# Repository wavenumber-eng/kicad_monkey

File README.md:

# KiCad Monkey

```text
            ▓▓▓▓▓▓▓▓▓▓
          ▓▓▓▓▓▓▓▓▓▓▓▓▓▓
        ▓▓▓▓▓▓▓▓▓▓▓▓▓▓▓▓▓▓
      ▓▓▓▓░░░░░░▓▓░░░░░░▓▓▓▓
  ░░░░▓▓░░░░░░░░░░░░░░░░░░▓▓░░░░
  ░░░░▓▓░░    ░░░░░░    ░░▓▓░░░░
    ░░▓▓░░  ██░░░░░░  ██░░▓▓░░
      ▓▓░░░░░░░░░░░░░░░░░░▓▓
        ▓▓░░░░░░░░░░░░░░▓▓
          ▓▓▓▓░░░░░░▓▓▓▓
  ░░          ▓▓▓▓▓▓
    ▓▓      ▓▓▓▓▓▓▓▓▓▓
    ▓▓▓▓    ▓▓▓▓▓▓▓▓▓▓
      ▓▓▓▓▓▓▓▓▓▓▓▓▓▓▓▓▓▓
          ▓▓▓▓░░▓▓░░▓▓▓▓
```

`kicad_monkey` is a focused Python package for KiCad source-file parsing,
round-trip modeling, close-to-format utilities, and IR-backed 2D rendering.

Use it when you need Python code to inspect or modify KiCad files directly:

- read `.kicad_pro`, `.kicad_sch`, `.kicad_pcb`, `.kicad_sym`, and
  `.kicad_mod` files;
- query schematic and PCB objects through typed model facades;
- compile KiCad-native design netlists and design JSON;
- render schematic, PCB, symbol, and footprint views through plotter IR and SVG;
- make focused model edits, then write KiCad files back out.

This package is the low-level parser/model/rendering library. The same
repository also contains the separately published `kicad-cruncher` workflow
CLI under `packages/kicad_cruncher/`. The CLI depends on Monkey; Monkey never
depends on the CLI.

The Rust port has closed its Plotter-IR boundary and its bounded Windows x64
native Cruncher delivery milestone. See
the [native Cruncher delivery audit](docs/design/rust-phase6-native-cruncher-audit.html).
The accepted [native base SVG slice](docs/design/rust-native-svg-phase6-slice.html)
is followed by the accepted
[Windows no-fallback PCB physical provider](docs/design/rust-native-physical-provider-phase6-slice.html),
which retains Cruncher-owned enrichment and composition while replacing its
physical-base serialization seam. The accepted
[source-bound native design-facts slice](docs/design/rust-native-design-facts-phase6-slice.html)
next switches the Windows compiled graph and version-E netlist while retaining
Python Design JSON, netlist JSON, presentation, and orchestration. The
[accepted native-backed CLI compatibility slice](docs/design/rust-native-full-cli-phase6-slice.html)
governs the installed entry points, primary design aliases, artifact tree,
logs, exits, and no-fallback failures without claiming a separate all-Rust
Cruncher executable. The accepted
[Windows x64 release exit](docs/design/rust-phase6-exit.html) binds one tested
candidate set to CI and release publication. That milestone remains the
historical native-provider boundary: Linux and macOS retained the established
Python provider path, and Python still owned Cruncher orchestration and
presentation.

The accepted
[pure-Rust design CLI follow-on](packages/kicad_cruncher/docs/design/rust-cli-phase7-audit.html)
now supersedes that boundary for the Windows x64 `design`, `design-review`, and
`dr` vertical slice. Release archives contain Python-free `kicad-cruncher` and
`kcr` executables that own the complete review-bundle orchestration and
transactional publication path, plus version reporting. This is deliberately
not an all-command or all-platform Rust claim: other Cruncher commands remain
available through the universal Python wheel and `python -m kicad_cruncher`,
and Monkey remains the reusable lower-level library rather than depending on
Cruncher.

## Install

For library use inside an existing Python environment:

```powershell
pip install kicad-monkey
```

For development:

```powershell
git clone https://github.com/wavenumber-eng/kicad_monkey.git
cd kicad_monkey
uv sync --extra test
```

To develop and validate both public distributions from one checkout:

```powershell
uv sync --all-packages --all-extras
uv run --package kicad-cruncher kicad-cruncher --help
uv run --all-packages --all-extras python -m pytest tests/cross_package -q
```

## Quick Examples

### Load A Design And Inspect Nets

```python
from kicad_monkey import KiCadDesign

design = KiCadDesign.from_project_file("hardware/demo.kicad_pro")
netlist = design.to_netlist()

for net in netlist.nets:
    terminals = ", ".join(
        f"{terminal.designator}.{terminal.pin}"
        for terminal in net.terminals
    )
    print(f"{net.name}: {terminals}")
```

Save the KiCad-native design JSON used by higher-level review tools:

```python
from pathlib import Path

Path("build").mkdir(parents=True, exist_ok=True)
design.save_json("build/design.json")
```

### Render PCB SVG

```python
from pathlib import Path

from kicad_monkey import KiCadDesign

design = KiCadDesign.from_project_file("hardware/demo.kicad_pro")

out_dir = Path("build/svg")
out_dir.mkdir(parents=True, exist_ok=True)

svg = design.to_pcb_svg(
    layers=["Edge.Cuts", "F.Cu", "F.SilkS"],
    profile="enriched",
)
(out_dir / "front-copper.svg").write_text(svg, encoding="utf-8")
```

Use `profile="oracle"` when comparing against KiCad CLI output. Use
`profile="enriched"` when an app needs metadata on SVG elements. PCB SVG
rendering builds the board render IR before applying `layers=`, so layer
filters reduce output size but do not avoid full PCB parse or IR-build cost.

### Render Every Schematic Sheet Instance

Hierarchical designs can instantiate one `.kicad_sch` file more than once.
`KiCadSchematicInstance` represents each concrete sheet view.

```python
from pathlib import Path

from kicad_monkey import KiCadDesign, render_ir_to_svg

design = KiCadDesign.from_project_file("hardware/demo.kicad_pro")

out_dir = Path("build/schematic-svg")
out_dir.mkdir(parents=True, exist_ok=True)

for sheet in design.schematic_instances():
    doc = design.to_schematic_instance_ir(sheet)
    svg = render_ir_to_svg(doc)
    safe_name = sheet.sheet_name.replace("/", "_").replace("\\", "_")
    (out_dir / f"{sheet.instance_index:02d}_{safe_name}.svg").write_text(
        svg,
        encoding="utf-8",
    )
```

To find where a reused child schematic appears:

```python
for instance in design.schematic_instances_for("hardware/LED_Controller.kicad_sch"):
    print(instance.sheet_name, instance.sheet_path, instance.sheet_instance_path)
```

### Query And Mutate Schematic Objects

The `.objects` property is a live read-only query view over model-owned
objects. Mutate the returned objects, then call `save()`.

```python
from kicad_monkey import KiCadSchematic

schematic = KiCadSchematic.from_file("hardware/demo.kicad_sch")

for symbol in schematic.objects.where("SchSymbol"):
    if symbol.reference.startswith("R"):
        symbol.set_property_value("Value", "10 kOhm")

for label in schematic.objects.where("SchLabel"):
    if label.effects is not None and label.effects.font is not None:
        label.effects.font.size_x = 1.5
        label.effects.font.size_y = 1.5

schematic.save("hardware/demo.edited.kicad_sch")
```

### Query And Mutate PCB Objects

```python
from kicad_monkey import KiCadPcb

board = KiCadPcb.from_file("hardware/demo.kicad_pcb")

for footprint in board.objects.where("Footprint"):
    reference = footprint.get_property_value("Reference")
    if reference.startswith("U"):
        footprint.set_property_value("Reviewed", "yes", create=True)

for text in board.objects.where("GrText", layer="F.SilkS"):
    text.effects.font.size_x = 1.0
    text.effects.font.size_y = 1.0
    text.text = text.text.strip()

board.save("hardware/demo.edited.kicad_pcb")
```

Object queries also work with class objects when you prefer typed imports:

```python
from kicad_monkey import Footprint, KiCadPcb

board = KiCadPcb.from_file("hardware/demo.kicad_pcb")
connectors = [
    footprint
    for footprint in board.objects.where(Footprint)
    if footprint.get_property_value("Reference").startswith("J")
]
```

### Scan Large Files Without Full Model Materialization

Use projection or targeted readers when you only need narrow inventories,
diagnostics, source spans, or selected object families from a large file.

```python
from kicad_monkey import KiCadPcbProjection

projection = KiCadPcbProjection.from_file("hardware/demo.kicad_pcb")

for model_ref in projection.model_references():
    print(model_ref.reference, model_ref.path)

route_count = len(projection.segments()) + len(projection.vias())
print(f"{route_count} route objects")
```

For schematic or custom narrow reads, use the generic targeted reader:

```python
from kicad_monkey import SchSymbol, iter_kicad_objects_from_file

for symbol in iter_kicad_objects_from_file("hardware/demo.kicad_sch", SchSymbol):
    print(symbol.reference, symbol.value)
```

Projection still scans the source file, but it hydrates only the requested
object families. Use `KiCadPcb`, `KiCadSchematic`, or `KiCadDesign` when you
need mutation, rendering, netlisting, full geometry, or cross-document context.
For measured tradeoffs, net-table caveats, and render cost details, see
[Project Workflows And Read-Path Selection](docs/guides/project-workflows.html).

## Testing

Rack is the primary public gate:

```powershell
uv run --extra test python tests/rack.py run L0_foundation
uv run --extra test python tests/rack.py run L99_signoff
```

The parser-first Rust port uses the same Rack orchestrator. Its L0 gate is
split into locked Cargo tests, shared Python/Rust vectors, generated-contract
and executable WASM signoff, and comparative performance evidence:

```powershell
uv run python tests/rack.py run L0_044
uv run python tests/rack.py run L0_045
uv run python tests/rack.py run L0_046
```

Performance cases `L0_047`, `L1_023`, and `L1_024` are advisory and skip in
ordinary fast/full development runs. Run them explicitly in the strict lane:

```powershell
uv run python tests/rack.py run L0_047 --lane strict
uv run python tests/rack.py run L1_023 --lane strict
uv run python tests/rack.py run L1_024 --lane strict
```

Run `npm ci` once to install the pinned TypeSpec toolchain. The executable WASM
test also requires the lock-compatible runner documented in
`docs/design/rust-standard.html`.

`L99_signoff` checks release metadata, changelog coverage, public API contract
resolution, API design-doc ownership, Rack test ownership, corpus archive
hygiene, and the current ruff/pyright ratchet state.

## KiCad Newstroke Webfonts

The authoritative `assets/fonts/` bundle contains the KiCad Stroke family as
Light, Regular, and Bold faces, each upright and italic, in TTF, OTF, WOFF,
and WOFF2 formats. The companion CSS and offline demo exercise electronics
notation, Greek, mathematical symbols, BOM text, and fabrication notes.

Regenerate and verify the complete bundle from the vendored CC0 Newstroke
table with:

```powershell
uv run python tools/package_kicad_stroke_webfont_assets.py
uv run python tools/package_kicad_stroke_webfont_assets.py --check
```

The checked manifest pins the generator, source table, mark, theme, every font
file, CSS, and demo. See [KiCad Newstroke Webfont Bundle](docs/design/kicad-stroke-webfont.html)
for the format and ownership decisions.

The redistributable KiCad corpus is restored locally as
`tests/corpus/kicad.zip`; the archive itself is ignored and is not tracked with
Git LFS. CI restores that archive from the public object URL recorded in
`tests/corpus/kicad.archive.toml` and verifies size and SHA-256 before tests run.
`KICAD_MONKEY_CORPUS_URL` may override the manifest URL for local testing or an
emergency reroute. The loose mirror is ignored locally; test helpers extract the
archive on demand when no external corpus is configured.

Restore and verify the archive before running mandatory corpus-backed Rust
parity gates:

```powershell
uv run --extra test python scripts/kicad_corpus_archive.py restore --check-zip
uv run --extra test python tests/rack.py run L1_029
```

## API Shape

Stable package-root exports are recorded in
`kicad_monkey.kicad_api_contract`. Those names are the public API that
downstream code should rely on. The broader package `__all__` remains a
discovery surface while downstream integrations prove which additional symbols
should become stable public exports.

The public OOP facade groups and supporting public classes are documented under
[docs/design/api](docs/design/api). Use
[Project Workflows And Read-Path Selection](docs/guides/project-workflows.html)
for practical guidance on which API to choose for project, render, inventory,
and large-file workflows. L99 fails when a stable public class or major
interface is missing design documentation or Rack test ownership.

Typical entrypoints:

```python
from kicad_monkey import KiCadDesign, KiCadFootprint, KiCadPcb, KiCadSchematic
from kicad_monkey import KiCadSymbolLib

schematic = KiCadSchematic.from_file("design.kicad_sch")
board = KiCadPcb.from_file("board.kicad_pcb")
design = KiCadDesign.from_project_file("project.kicad_pro")
symbols = KiCadSymbolLib.from_file("library.kicad_sym")
footprint = KiCadFootprint.from_file("package.kicad_mod")
```

For workflow-level API choice, use
[Project Workflows And Read-Path Selection](docs/guides/project-workflows.html)
as the canonical guide.

## Fixture Model

Public fixtures should be redistributable and package-local when possible.
Broader fixture families should use this shape:

- `input/`
- `reference_output/`
- `output/`

`output/` is transient and should stay local or temporary.

## Documentation

- [User Guides](docs/guides)
- [Architecture Decision Records](docs/adrs)
- [Design Notes](docs/design)
- [Changelog](CHANGELOG.md)
- [Contributing](CONTRIBUTING.md)

## License

MIT.

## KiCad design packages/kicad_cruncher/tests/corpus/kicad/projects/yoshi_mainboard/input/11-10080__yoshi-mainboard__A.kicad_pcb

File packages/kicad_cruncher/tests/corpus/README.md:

# Test Corpus

This directory holds redistributable KiCad fixtures used by public
`kicad-cruncher` workflow tests.

The current copied fixtures are:

- `kicad/projects/hlr_test`
- `kicad/projects/taillight/input`
- `kicad/projects/charge_indicator/input`
- `kicad/projects/yoshi_mainboard/input`
- `kicad/projects/speedy_processing_module/input`
- `kicad/projects/4-ch-backplane/input`
- `kicad/projects/cutout_test`

Each fixture is copied from the cleaned public `kicad-monkey` corpus. The
directory shape mirrors the source corpus so future fixtures can be compared or
refreshed without changing test lookup constants.

`speedy_processing_module/input` intentionally carries only the project root,
board, and schematic files referenced by the active sheet hierarchy. Stale or
unreferenced scratch schematics from the expanded source corpus are omitted.

`hlr_test` is a focused single-component assembly projection fixture with an
embedded STEP model and non-default model offset/rotation.

`4-ch-backplane/input` is a sanitized real-world hierarchical project with
replicated sheet instances and an off-board USB sheet. It is kept as a netlist
and design-review regression fixture.

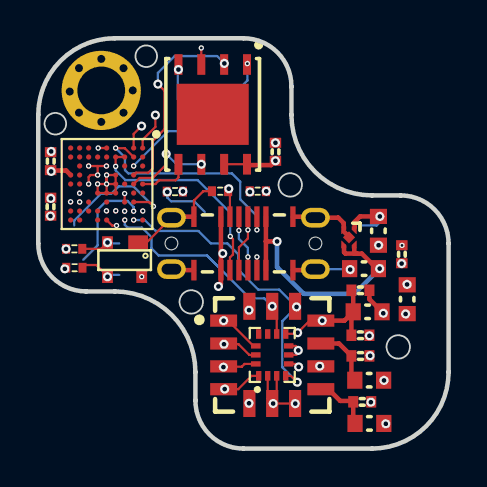
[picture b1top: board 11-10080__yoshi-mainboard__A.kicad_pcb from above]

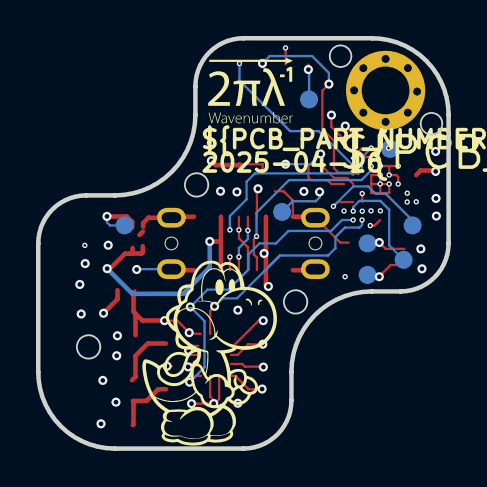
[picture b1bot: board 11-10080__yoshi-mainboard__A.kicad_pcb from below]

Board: 6 copper layers, 22.8 x 22.8 mm, 35 parts (8 on the bottom side), 28 nets.

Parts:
C1, C2, C5, C6, C7, C9, C10, C12: 0.1µF; C0402_0.55MM_MD
C3, C4: 1µF; C0603_0.90MM_MD
C11, C13, C14, C16: 2.2µF; C0603_0.90MM_MD
J1: USB4145-03-0230-C
M1: M2.2
R1, R2, R5: 5.1kΩ; R0402_0.40MM_HD
R3, R4: 33Ω; R0402_0.40MM_HD
TP1, TP2, TP3, TP4, TP5, TP6, TP7, TP8: SMT Testpoint 35mil; SMT_TP-1MM
U1: MCXA156VMP; LFBGA64
U2: ADXL355BEZ-RL7; LCC14P127_600X600X225L91X50N
U3: IIM-42352; PQFN50P250X300X97-14N
U5: PRTR5V0U2X,215; SOT143B
U6: W25Q128JVPIQ; SON127P600X80_HS-9N
U9: TPS7A2033DQNR; X2SON

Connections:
+3v3: C1.2 (1), C2.2 (1), C3.2 (1), C5.2 (1), C6.2 (1), C7.2 (1), C9.2 (1), C14.2 (1), C16.2 (1), R5.2, TP4.1, U1.E3 (VDD_ANA), U1.F4 (VREFH), U1.G3 (VDD), U1.G5 (VDD_P3), U1.H6 (VDD_USB), U1.J4 (P2_12/USB0_VBUS_DET), U2.5 (VDDIO), U2.11 (VSUPPLY), U3.5 (VDDIO), U3.8 (VDD), U6.3 (~WP_(IO2)), U6.7 (~HOLD_(IO3)), U6.8 (VCC), U9.1 (OUT)
+VBUS: C4.2 (1), J1.A4 (VBUS_A), J1.A9 (VBUS_A), J1.B4 (VBUS_B), J1.B9 (VBUS_B), U5.4 (VCC), U9.3 (EN), U9.4 (IN)
/ACCEL-CS: U1.E9 (P3_11/TRIG_IN6/LPSPI1_PCS0/LPUART1_CTS_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), U2.1 (~CS/SCL), U3.12 (AP-CS)
/ACCEL-MISO: U1.D8 (P3_9/TRIG_IN4/LPSPI1_SDI/LPUART1_TXD/CT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), U2.4 (MISO/ASEL), U3.1 (AP-SDO/AP-AD0)
/ACCEL-MOSI: U1.C8 (P3_8/TRIG_IN3/LPSPI1_SDO/LPUART1_RXD/CT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), U2.3 (MOSI/SDA), U3.14 (AP-SDA/AP-SDIO/AP-SDI)
/ACCEL-SCK: U1.E8 (P3_10/TRIG_IN5/LPSPI1_SCK/LPUART1_RTS_B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), U2.2 (SCLK/VSSIO), U3.13 (AP-SCL/AP-SCLK)
/CC1: J1.A5 (CC1), R2.2, U1.A1 (P1_6/TRIG_IN2/LPSPI0_PCS1/LPUART2_RTS_B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)
/CC2: J1.B5 (CC2), R1.2, U1.B1 (P1_7/TRIG_OUT2/LPUART2_CTS_B/CT_INP7/CT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)
/DRDY: U1.A8 (P3_0/TRIG_IN0/LPUART3_RXD/CT_INP16/PWM0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), U2.14 (DRDY)
/FLASH-CS: U1.B3 (P1_3/TRIG_OUT1/LPSPI0_PCS0/LPI2C1_SCLS/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), U6.1 (~CE)
/FLASH-MISO: U1.B4 (P1_2/TRIG_OUT0/LPSPI0_SDI/LPI2C1_SDAS/C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), U6.2 (SO_(IO1))
/FLASH-MOSI: U1.A5 (P1_0/TRIG_IN0/LPSPI0_SDO/LPI2C1_SDA/CT_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), U6.5 (SI_(IO0))
/FLASH-SCLK: U1.B5 (P1_1/TRIG_IN1/LPSPI0_SCK/LPI2C1_SCL/CT_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), U6.6 (SCK)
/INT1: U1.B9 (P3_6/CLKOUT/LPSPI1_PCS3/LPUART3_RTS_B/C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), U2.12 (INT1), U3.4 (INT1/INT)
/INT2/CLKIN: U1.C9 (P3_7/TRIG_IN2/LPSPI1_PCS2/LPUART3_CTS_B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), U2.13 (INT2), U3.9 (INT2/FSYNC/CLKIN)
/SBU1: J1.A8 (SBU1), U1.B2 (P1_8/FREQME_CLK_IN0/LPUART1_RXD/LPI2C2_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), U1.D1 (P1_11/TRIG_OUT2/LPUART1_CTS_B/LPI2C2_SC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)
/SBU2: J1.B8 (SBU2), U1.C2 (P1_9/FREQME_CLK_IN1/LPUART1_TXD/LPI2C2_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), U1.D2 (P1_10/LPUART1_RTS_B/LPI2C2_SDAS/CT2_MAT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)
/USB-DM: J1.A7 (DN1), J1.B7 (DN2), R3.2, TP6.1, U5.3 (IO2)
/USB-DP: J1.A6 (DP1), J1.B6 (DP2), R4.2, TP7.1, U5.2 (IO1)
GND: C1.1, C2.1, C3.1, C4.1, C5.1, C6.1, C7.1, C9.1, C10.1, C11.1, C12.1, C13.1, C14.1, C16.1, J1.A1 (GND_A), J1.A12 (GND_A), J1.B1 (GND_B), J1.B12 (GND_B), J1.S1 (SHIELD), J1.S2 (SHIELD), J1.S3 (SHIELD), J1.S4 (SHIELD), M1.1, R1.1, R2.1, TP5.1, U1.D4 (VSS), U1.D5 (VSS), U1.D6 (VSS), U1.E4 (VREFL), U1.E6 (VSS), U1.F5 (VSS), U1.F6 (VSS), U2.6 (VSSIO), U2.7 (RSV), U2.9 (VSS), U3.2 (RESV), U3.3 (RESV), U3.6 (GND), U3.7 (RESV), U5.1 (GND), U6.4 (GND), U9.2 (GND), U9.5 (GND)
unnamed: R5.1, TP8.1, U1.C7 (P0_6/ISPMODE_N)
unnamed: TP3.1, U1.E1 (P1_29/RESET_B/SPC_LPREQ)
unnamed: TP1.1, U1.B7 (SWCLK/P0_1)
unnamed: TP2.1, U1.B8 (SWDIO/P0_0)
unnamed: R3.1, U1.H7 (USB0_DM)
unnamed: R4.1, U1.J7 (USB0_DP)
unnamed: C10.2 (1), C11.2 (1), U2.10 (V1P8ANA)
unnamed: C12.2 (1), C13.2 (1), U2.8 (V1P8DIG)

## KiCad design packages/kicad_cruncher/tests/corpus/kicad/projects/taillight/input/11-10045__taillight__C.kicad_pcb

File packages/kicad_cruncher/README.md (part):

# KiCad Cruncher

`kicad-cruncher` is a cross-platform command-line application for KiCad design
workflows. It consumes the public `kicad-monkey` package and keeps higher-level
CLI behavior outside the core parser package.

The public commands generate KiCad-native design review bundles, project-local
library bundles, cleaned library-ingestion bundles, project health reports, PCB
SVG/STEP review artifacts, plugin tooling, and BOM/PnP/JLC manufacturing
outputs from public `kicad-monkey` parsers/renderers.

## Install

Install `uv` first if it is not already available:

```powershell
powershell -ExecutionPolicy ByPass -c "irm https://astral.sh/uv/install.ps1 | iex"
```

On macOS or Linux:

```bash
curl -LsSf https://astral.sh/uv/install.sh | sh
```

Install as a uv tool:

```powershell
uv tool install kicad-cruncher
uv tool update-shell
kicad-cruncher --help
```

During local development:

```powershell
git clone https://github.com/wavenumber-eng/kicad_monkey.git
cd kicad_monkey
uv sync --all-packages --all-extras
uv run --package kicad-cruncher kicad-cruncher --help
uv run --package kicad-cruncher python -m kicad_cruncher version
```

Within the universal wheel's Python module path, Windows x64 selects the
installed Monkey wheel's `kicad-monkey-native` sidecar for PCB physical-base
SVG, compiled schematic graphs, and version-E netlists; a native failure is
terminal and is never retried through the corresponding Python implementation.
Linux and macOS retain the Python providers for that module path. The
`KICAD_CRUNCHER_NATIVE_DESIGN_FACTS=1` and
`KICAD_CRUNCHER_NATIVE_PHYSICAL=1` environment switches are development/test
opt-ins on other platforms, not production-support declarations.

### Pure-Rust design CLI on Windows x64

Each Cruncher GitHub release now includes a hash-manifested
`kicad-cruncher-<version>-windows-x64.zip`. Extract it and put that directory
before Python tool-script directories on `PATH` to select the pure-Rust
`kicad-cruncher.exe` and `kcr.exe`, accompanied by the qualified
`geometer.exe` model-geometry sidecar. The Cruncher entry points currently own
`design`, `design-review`, `dr`, `toon`, and `--version`; they generate the
complete review bundle or native board illustrations without a Python
interpreter.

The same Rust client and released Geometer process are compiled and exercised
in CI on Linux x64, Linux ARM64, and macOS ARM64. Those platforms are currently
source-build targets; only the Windows x64 native archive is promoted as a
release candidate.

For a source checkout, the equivalent tested install is:

```powershell
cargo install --locked `
  --path packages/kicad_cruncher/src/rs/kicad-cruncher-cli `
  --root .native-cruncher --force --bins
$env:PATH = "$PWD\.native-cruncher\bin;$env:PATH"
kcr design-review board.kicad_pro
```

The universal Python wheel remains the cross-platform distribution for the
full command set below and retains its public `kicad-monkey` dependency. Until
another command receives its own Rust vertical slice, invoke it explicitly as
`python -m kicad_cruncher <command>` when the native directory is first on
`PATH`.

## Commands

Run `python -m kicad_cruncher <command> --help` for the full Python command
set. The promoted Rust executable accepts the design aliases documented above.

| Command | Purpose | Status |
| --- | --- | --- |
| `bom` | Generate KiCad BOM outputs with shared field alias coalescing, variant-aware DNP handling, grouped JSON/CSV/XLSX review tables, and JLC BOM rows. | Public |
| `daemon` | Run the local plugin daemon and browser tool center used by KiCad IPC plugin workflows. | Public |
| `design` | Generate a design review bundle with KiCad-native design JSON, schematic SVGs, PCB copper-layer SVGs, a manifest, and a README for agents. Aliases: `design-review`, `dr`. | Public |
| `health` | Scan active project assets, model references, and project-listed local libraries without recursively importing unrelated library folders. | Public |
| `jlc` | Generate paired JLCPCB BOM XLSX and CPL XLSX upload workbooks from the shared BOM/PnP normalization layer. | Public |
| `kicad` | Inspect local KiCad installs, running KiCad-family processes, preferences, launch commands, and opt-in stop plans. | Public |
| `lib-extract` | Generate a cleaned lib_cruncher/Alexandria ingestion bundle with stripped symbols, footprints, optional models, and separated metadata JSON. Alias: `library-extract`. | Public |
| `megamaid` | Aggressively dissect a KiCad project into library artifacts, embedded assets, models, design review artifacts, netlists, SVGs, manifests, and README output. | Public |
| `pcb` | Run PCB utility commands, including config-driven PCB cleanup planning and explicit direct-file apply. | Public |
| `pcb-layer-step` | Generate compact colored STEP models for fixture-alignment checks on one KiCad PCB layer. | Public |
| `pcb-svg` | Generate PCB layer SVG artifacts and configured design views, including geometer-backed assembly HLR overlays. | Public |
| `plugin` | Install, inspect, and remove bundled KiCad IPC plugin packages. | Public |
| `pnp` | Generate KiCad pick-and-place JSON, CSV, XLSX, and JLC CPL outputs using component-center coordinates relative to the aux axis/drill-place file origin. | Public |
| `project` | Scaffold a new KiCad project (`.kicad_pro` + top-level `.kicad_sch`, optional embedded worksheet, library tables, PCB, title-block metadata, and text variables) from flags, a JSONC config, or the interactive `--tui` form. | Public |
| `project-lib` | Extract metadata-preserving project-local symbol and footprint libraries, defaulting to `./local-library/` and updating project library tables by default. Aliases: `project-library`, `project-local-lib`, `local-library`. | Public |
| `schematic` | Run schematic utility commands, currently exposing the deferred schematic cleanup planning stub. | Public |
| `version` | Print `kicad-cruncher` and controlled dependency versions. | Public |

The `design` command writes to `./output/design/` by default. Its aliases
`design-review` and `dr` produce the same output:

```powershell
kicad-cruncher design board.kicad_pro
kicad-cruncher design-review board.kicad_pro
kicad-cruncher dr board.kicad_sch --no-indexes
kicad-cruncher design -o output/design
```

The design review output includes `<input-stem>_design.json`, the exact
`<input-stem>_compiled_schematic_graph.json` embedded in that Design JSON,
`design_review_manifest.json`, `README.md`, enriched black-and-white schematic
SVGs under `schematics/`, and one PCB review SVG per copper layer under
`pcb/copper_layers/` when a board is present. Schematic review SVGs preserve
the `kicad-monkey` enrichment metadata while applying the
`kicad_cruncher.design_review.schematic_svg.a0` black-and-white role theme.
Each schematic SVG identifies its canonical graph page and carries forward and
reverse indexes between source-owned SVG ids and compiled-graph targets. Agents
should join with `page_occurrence_ref + artifact_key + element_id`, then follow
terminal/local-net and hierarchy-binding refs; names, text, geometry, and DOM
order are not connectivity keys. `--no-indexes` removes only the optional
legacy Design JSON indexes and retains this graph linkage.
PCB review SVGs include the copper layer, `Edge.Cuts`, and `kicad-monkey`
enriched drill/slot records.
Plated pads and vias, and KiCad `np_thru_hole` mechanical pads, are
distinguished with `data-hole-plating` and `data-hole-kind` attributes.
Design-review styling colors those existing records in place: plated drills are
blue, plated slots are cyan, non-plated drills are red, and non-plated slots are
orange. KiCad Cruncher does not add a second drill/slot overlay or duplicate
the `kicad-monkey` plating metadata.

For large boards, `design`/`design-review`/`dr` still produce full design JSON
and netlist artifacts, so they intentionally materialize broad project state.
The PCB review SVG pass reuses a command-scoped cached board render state while
writing one SVG per copper layer. On public corpus measurements with
`kicad-monkey 2026.7.17`, this mainly helps boards with several copper layers;
the full design JSON artifact can still dominate total runtime on smaller
layer counts.

The `pcb-svg` command writes to `./output/pcb-svg/` by default and uses
`pcb.svg.config` JSON/JSONC configs compatible with the A0 PCB SVG view
contract. This remains a preview feature: SVG structure,
virtual-layer metadata, default views, and config controls may change as more
real-world boards are tested.

Artifact publication is transactional: failed rendering leaves a new output
directory absent and preserves an existing output tree byte-for-byte. When the
project-adjacent `pcb.svg.config` is missing, the command intentionally authors
that config template before rendering; it is configuration input and is not
part of the transient artifact transaction.

```powershell
kicad-cruncher pcb-svg board.kicad_pcb
kicad-cruncher pcb-svg project.kicad_pro --views assembly-top
kicad-cruncher pcb-svg board.kicad_pcb --config pcb.svg.config -o output/pcb-svg
```

`pcb-svg` composes KiCad Monkey enriched physical layer SVG with explicit
virtual layers. `BOARD_OUTLINE` and `BOARD_CUTOUTS` are synthesized from closed
`Edge.Cuts` regions, with derived arc/curve/circle smoothness controlled by
`styles.board_outline.max_*_segment_mm`, `DRILLS` and `SLOTS` preserve KiCad
Monkey hole metadata, `PIN1_TOP`/`PIN1_BOTTOM` add configurable pad-linked
marker groups, and
`ASSEMBLY_HLR_TOP`/`ASSEMBLY_HLR_BOTTOM` append geometer-backed STEP hidden-line
overlays or footprint-bound fallbacks. The assembly silhouette mode is named
`outline` and uses Geometer's mesh-shadow outline algorithm by default. Use
`outline`; legacy `simple` config values are no longer accepted. Default assembly views include
only top and bottom assembly outputs. They include board cutouts, drills, slots,
pin-1 markers, Geometer `outline` HLR with hole-first bounds fallback, and
aspect-preserving fitted `ASSEMBLY_DESIGNATORS_TOP`/
`ASSEMBLY_DESIGNATORS_BOTTOM` labels drawn above the 75% opacity HLR/bounds
overlay. Assembly labels are blue, bold monospace by default and rotate 90
degrees in the configurable `ccw`/`cw` direction when their fitted bounds exceed
the configurable height/width aspect threshold. Assembly designator style
overrides can target exact refs, prefixes, wildcards, or ranges.

The native `toon` command writes portable, digest-indexed SVGs and a
`manifest.json` to `./output/toon/` by default. It replaces that directory only
after every requested side has rendered successfully. Bottom views are mirrored
for presentation, and standard pad mask apertures honor resolved board,
footprint, and pad solder-mask margins, including negative pullback.
Its default presentation follows the Altium Cruncher Toon contract: the saved
side-specific stackup mask color at 75% opacity (off-white fallback), contrasting
silkscreen, light-gray drill/slot virtual layers, and 0.025/0.01375 mm Geometer HLR outline/detail
widths. `BOARD_SUBSTRATE` is a distinct `#B6A26B` board-domain fill below copper
and solder mask. Physical drills, slots, and internal cutouts are subtracted from
that substrate; colored drill/slot virtual objects are then painted without a
stroke. Those objects are clipped only to the physical board domain so holes
crossing the outer profile or an interior cutout appear as castellated partial
holes.

```powershell
kcr toon board.kicad_pcb
kcr toon project.kicad_pro --side top -o output/toon
kcr toon board.kicad_pcb --side bottom
kcr toon board.kicad_pcb --theme black
kcr toon board.kicad_pcb --soldermask-color '#000000'
kcr toon --write-config toon.config
kcr toon board.kicad_pcb --config toon.config
kcr toon board.kicad_pcb --workers 4 --timings output/toon-profile.json
kcr toon board.kicad_pcb --cache-dir temp/toon-cache
kcr toon board.kicad_pcb --no-cache
kcr toon board.kicad_pcb --footprint U1
kcr toon project.kicad_pro --assembly --variant ADXL355
kcr toon project.kicad_pro --all-variants
```

Toon uses the Altium-compatible `saved`, `white`, `black`, `blue`, `red`,
`purple`, `yellow`, and `green` mask/silk themes. Without an explicit theme it
loads `toon.config` beside the board, creating an editable JSONC preset there
when missing. `--config` selects another PCB-SVG config and `--write-config`
writes the resolved preset without loading a board or starting Geometer.
Explicit `--theme` or `--soldermask-color` is applied after the authored file.
The native compositor consumes the preset's substrate, copper, mask, silk,
cutout, drill/slot, outline, and illustration lineweight/opacity settings.
Each enabled top/bottom view may override those styles and controls its painter
order and layer omissions through its `layers` list. Explicit CLI colors remain
the final override for both views.

`--assembly` adds an independent red assembly-designator layer after each
side's model illustration layer. The shared Rust fitter follows PCB Autodoc's
polygon candidate search, binary maximum-size fit, two-axis rotation, size cap,
fill ratio, and horizontal tie preference. It fits against projected model
outlines and falls back to visible electrical-pad envelopes only for footprints
without an authored model. Component config entries with
`show_designator: false` suppress individual labels.

Project inputs support `--variant NAME` and `--all-variants`. Variant DNP
components retain their physical board pads but omit model illustrations and
assembly labels. A named selection is written under its portable variant
directory; all-variants writes `base` plus every project variant in separate
directories. Geometry/model caches remain shared across those outputs, and the
manifest/timing contracts record the variant selection and exact per-variant
SVG digests. `--doc`/`--pcbdoc` selects an adjacent board by name when a project
contains a non-default board filename.

`--footprint REF` emits one transparent, tightly fitted Toon SVG for the exact
placed footprint and its embedded models. It preserves the footprint's board
rotation and side, includes only its copper, silkscreen, drills and slots, and
does not leak neighboring board geometry. The side is inferred; an explicit
opposite `--side` is rejected. The artifact name includes the reference, for
example `board__U1__toon_top.svg`.

Toon illustrates each unique model content/effective-pose request once per job
and schedules cache misses over a bounded Geometer pool (`--workers`, default
4). Successful geometry is cached across invocations; failures are retried and
are never positive cache entries. The default cache is
`%LOCALAPPDATA%\kicad-cruncher\toon-models-a0` on Windows,
`~/Library/Caches/kicad-cruncher/toon-models-a0` on macOS, and
`$XDG_CACHE_HOME/kicad-cruncher/toon-models-a0` (or
`~/.cache/kicad-cruncher/toon-models-a0`) on Linux. `--no-cache` disables only
the persistent layer. A fully warm render does not launch Geometer.

`--timings PATH` writes the portable `kicad_cruncher.toon_timings.a0` JSON
contract with phase durations, requested/started workers, cache mode and hit
counts, request counts, warnings, output sizes, SVG digests, and the portable
resolved-config digest also recorded in the Toon manifest.

The command discovers the qualified Geometer executable beside `kcr` or via
`GEOMETER_EXECUTABLE`. Native Toon currently consumes embedded STEP/STP models
from footprint or board scope. It does not resolve project-relative paths,
`${KIPRJMOD}`, absolute paths, or KiCad 3D-model environment variables while
rendering; those references are reported and omitted. The planned
[source-preserving model-embedding workflow](https://github.com/wavenumber-eng/kicad_monkey/issues/90)
can make resolvable external references available to Toon without adding a
second path-resolution system to the renderer. Custom/trapezoid mask polygon
offsets also remain outside this initial contract.

The `bom`, `pnp`, and `jlc` commands provide initial KiCad manufacturing output
support. They share a documented `bom.config` JSONC file with a top block
summary, generated per-field comments, field aliases for
manufacturer/part/JLC/value/description/footprint parameters, variant
selection, DNP policy, grouping fields, PnP table fields, and output path
templates.

```powershell
kicad-cruncher bom project.kicad_pro
kicad-cruncher pnp project.kicad_pro --format xlsx
kicad-cruncher jlc project.kicad_pro --variant ADXL355
kicad-cruncher bom --write-config bom.config
```

PnP and JLC CPL output use the documented `component-center` mode, which maps to
KiCad's footprint placement point relative to the aux axis, also called the
drill/place file origin. Alternate geometric centroid modes are not exposed in
this release.

The `pcb-layer-step` command writes fixture-alignment STEP artifacts under
`./output/pcb-layer-step/` by default. The generated config is intentionally
comment-heavy and can enable tracks, arcs, poured copper, vias, component pads,
board outline/cutout bodies, drill overlays, and fused copper review bodies.

```powershell
kicad-cruncher pcb-layer-step board.kicad_pcb
kicad-cruncher pcb-layer-step project.kicad_pro --doc board.kicad_pcb --layer bottom
kicad-cruncher pcb-layer-step --init-config --config pcb-layer-step.jsonc
```

## Output Layout

Output-producing commands follow the same directory policy:

- when `-o/--output` is omitted, write artifacts under `./output/<command>/`;
- when `-o/--output` is supplied, use that directory directly;
- command modules own filenames inside their command output directory.

## Tests

Run the Rack suite:

```powershell
uv run --extra test rack run --all
```

Run build and installed-console smoke tests:

```powershell
uv run --extra test python -m build
uv run --extra test twine check dist/*
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
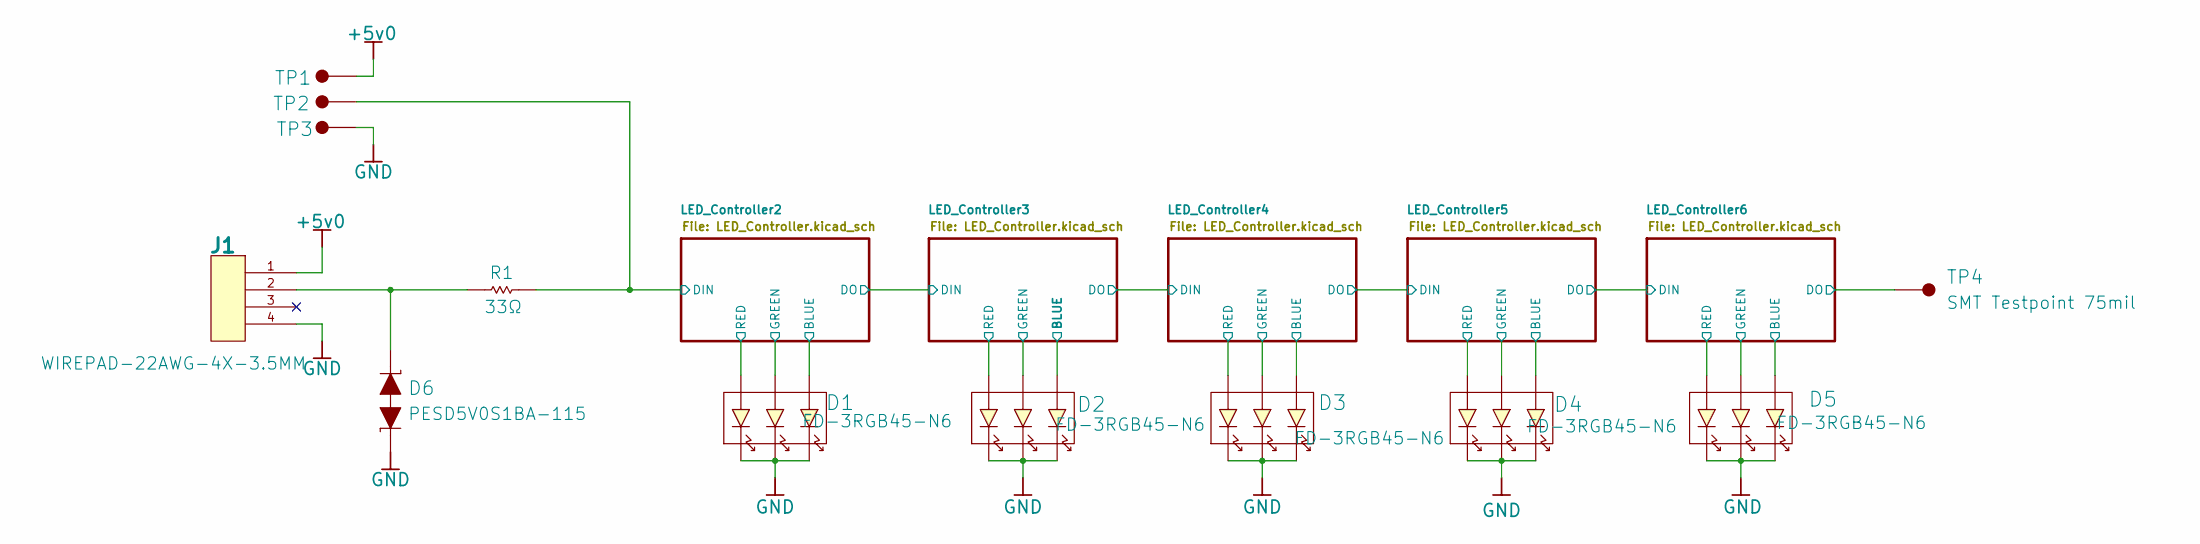
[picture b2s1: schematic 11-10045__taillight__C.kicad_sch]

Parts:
D1: FD-3RGB45-N6; Manufacturer Part Number FD-3RGB45-N6
D2, D3, D4, D5: FD-3RGB45-N6; MANUFACTURER PART NUMBER FD-3RGB45-N6; JLCPCB PART # C9900149223
D6: PESD5V0S1BA-115; D_SOD-323_P; Manufacturer Part Number PESD5V0S1BA-115
J1: WIREPAD-22AWG-4X-3.5MM; Manufacturer Part Number WIREPAD-22AWG-4X-3.5MM
R1: 33Ω; R0603_0.55MM_MD; Manufacturer Part Number ERJ-3EKF33R0V
TP1, TP2, TP3, TP4: SMT Testpoint 75mil; SMT_TP-75; Manufacturer Part Number SMT_TP-75

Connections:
+5v0: J1.1, TP1.1; also elsewhere on the board
/LED_Controller2/BLUE: D1.B+; also elsewhere on the board
/LED_Controller2/DIN: R1.2, TP2.1; also elsewhere on the board
/LED_Controller2/GREEN: D1.G+; also elsewhere on the board
/LED_Controller2/RED: D1.R+; also elsewhere on the board
/LED_Controller3/BLUE: D2.B+; also elsewhere on the board
/LED_Controller3/GREEN: D2.G+; also elsewhere on the board
/LED_Controller3/RED: D2.R+; also elsewhere on the board
/LED_Controller4/BLUE: D3.B+; also elsewhere on the board
/LED_Controller4/GREEN: D3.G+; also elsewhere on the board
/LED_Controller4/RED: D3.R+; also elsewhere on the board
/LED_Controller5/BLUE: D4.B+; also elsewhere on the board
/LED_Controller5/GREEN: D4.G+; also elsewhere on the board
/LED_Controller5/RED: D4.R+; also elsewhere on the board
/LED_Controller6/BLUE: D5.B+; also elsewhere on the board
/LED_Controller6/DO: TP4.1; also elsewhere on the board
/LED_Controller6/GREEN: D5.G+; also elsewhere on the board
/LED_Controller6/RED: D5.R+; also elsewhere on the board
GND: D1.B-, D1.G-, D1.R-, D2.B-, D2.G-, D2.R-, D3.B-, D3.G-, D3.R-, D4.B-, D4.G-, D4.R-, D5.B-, D5.G-, D5.R-, D6.1 (C), J1.4, TP3.1; also elsewhere on the board
unnamed: D6.2 (C), J1.2, R1.1

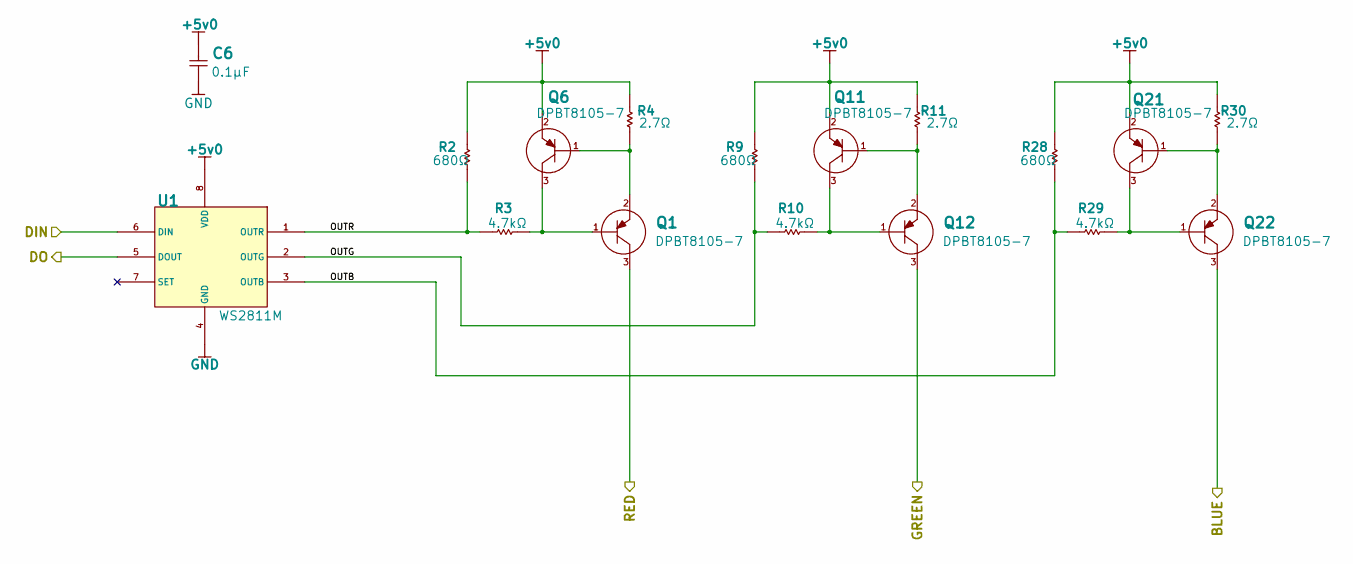
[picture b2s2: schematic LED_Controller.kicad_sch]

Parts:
C6: 0.1µF; C0603_0.90MM_MD; Manufacturer Part Number GCJ188R71C104KA01D
Q1, Q6, Q11, Q12, Q21, Q22: DPBT8105-7; SOT-23; Manufacturer Part Number DPBT8105-7
R2, R9, R28: 680Ω; R0603_0.55MM_HD; Manufacturer Part Number ERJ-3EKF6800V; JLCPCB Part # C226728
R3, R10, R29: 4.7kΩ; R0603_0.55MM_HD; Manufacturer Part Number ERJ-3EKF4701V
R4, R11, R30: 2.7Ω; R0805_0.70MM_HD; Manufacturer Part Number ERJ-6RQF2R7V; JLCPCB Part # C2933542
U1: WS2811M; MSOP8; Manufacturer Part Number WS2811M; JLCPCB Part # C3034986

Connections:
+5v0: C6.2 (1), Q6.2 (E), Q11.2 (E), Q21.2 (E), R2.1, R4.1, R9.1, R11.1, R28.1, R30.1, U1.8 (VDD); also elsewhere on the board
/LED_Controller2/DO: U1.6 (DIN); also elsewhere on the board
/LED_Controller3/BLUE: Q22.3 (C); also elsewhere on the board
/LED_Controller3/DO: U1.5 (DOUT); also elsewhere on the board
/LED_Controller3/GREEN: Q12.3 (C); also elsewhere on the board
/LED_Controller3/OUTB: R28.2, R29.1, U1.3 (OUTB)
/LED_Controller3/OUTG: R9.2, R10.1, U1.2 (OUTG)
/LED_Controller3/OUTR: R2.2, R3.1, U1.1 (OUTR)
/LED_Controller3/RED: Q1.3 (C); also elsewhere on the board
GND: C6.1, U1.4 (GND); also elsewhere on the board
unnamed: Q1.1 (B), Q6.3 (C), R3.2
unnamed: Q1.2 (E), Q6.1 (B), R4.2
unnamed: Q11.1 (B), Q12.2 (E), R11.2
unnamed: Q11.3 (C), Q12.1 (B), R10.2
unnamed: Q21.1 (B), Q22.2 (E), R30.2
unnamed: Q21.3 (C), Q22.1 (B), R29.2

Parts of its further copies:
C7, C8, C9, C10: 0.1µF; C0603_0.90MM_MD; Manufacturer Part Number GCJ188R71C104KA01D
Q2, Q3, Q4, Q5, Q7, Q8, Q9, Q10, Q13, Q14, Q15, Q16, Q17, Q18, Q19, Q20, Q23, Q24, Q25, Q26, Q27, Q28, Q29, Q30: DPBT8105-7; SOT-23; Manufacturer Part Number DPBT8105-7
R5, R6, R7, R8, R15, R18, R21, R26, R33, R37, R40, R45: 4.7kΩ; R0603_0.55MM_HD; Manufacturer Part Number ERJ-3EKF4701V
R12, R13, R17, R20, R22, R25, R31, R32, R36, R39, R42, R43: 680Ω; R0603_0.55MM_HD; Manufacturer Part Number ERJ-3EKF6800V; JLCPCB Part # C226728
R14, R16, R19, R23, R24, R27, R34, R35, R38, R41, R44, R46: 2.7Ω; R0805_0.70MM_HD; Manufacturer Part Number ERJ-6RQF2R7V; JLCPCB Part # C2933542
U2, U3, U4, U5: WS2811M; MSOP8; Manufacturer Part Number WS2811M; JLCPCB Part # C3034986

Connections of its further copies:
+5v0: C7.2 (1), C8.2 (1), C9.2 (1), C10.2 (1), Q7.2 (E), Q8.2 (E), Q9.2 (E), Q10.2 (E), Q13.2 (E), Q15.2 (E), Q17.2 (E), Q19.2 (E), Q23.2 (E), Q25.2 (E), Q27.2 (E), Q29.2 (E), R12.1, R13.1, R14.1, R16.1, R17.1, R19.1, R20.1, R22.1, R23.1, R24.1, R25.1, R27.1, R31.1, R32.1, R34.1, R35.1, R36.1, R38.1, R39.1, R41.1, R42.1, R43.1, R44.1, R46.1, U2.8 (VDD), U3.8 (VDD), U4.8 (VDD), U5.8 (VDD); also elsewhere on the board
/LED_Controller2/BLUE: Q26.3 (C); also elsewhere on the board
/LED_Controller2/DIN: U3.6 (DIN); also elsewhere on the board
/LED_Controller2/DO: U3.5 (DOUT); also elsewhere on the board
/LED_Controller2/GREEN: Q16.3 (C); also elsewhere on the board
/LED_Controller2/OUTB: R36.2, R37.1, U3.3 (OUTB)
/LED_Controller2/OUTG: R17.2, R18.1, U3.2 (OUTG)
/LED_Controller2/OUTR: R6.1, R22.2, U3.1 (OUTR)
/LED_Controller2/RED: Q3.3 (C); also elsewhere on the board
/LED_Controller3/DO: U4.6 (DIN); also elsewhere on the board
/LED_Controller4/BLUE: Q28.3 (C); also elsewhere on the board
/LED_Controller4/DO: U4.5 (DOUT), U5.6 (DIN)
/LED_Controller4/GREEN: Q18.3 (C); also elsewhere on the board
/LED_Controller4/OUTB: R39.2, R40.1, U4.3 (OUTB)
/LED_Controller4/OUTG: R20.2, R21.1, U4.2 (OUTG)
/LED_Controller4/OUTR: R7.1, R32.2, U4.1 (OUTR)
/LED_Controller4/RED: Q4.3 (C); also elsewhere on the board
/LED_Controller5/BLUE: Q30.3 (C); also elsewhere on the board
/LED_Controller5/DO: U2.6 (DIN), U5.5 (DOUT)
/LED_Controller5/GREEN: Q20.3 (C); also elsewhere on the board
/LED_Controller5/OUTB: R43.2, R45.1, U5.3 (OUTB)
/LED_Controller5/OUTG: R25.2, R26.1, U5.2 (OUTG)
/LED_Controller5/OUTR: R8.1, R42.2, U5.1 (OUTR)
/LED_Controller5/RED: Q5.3 (C); also elsewhere on the board
/LED_Controller6/BLUE: Q24.3 (C); also elsewhere on the board
/LED_Controller6/DO: U2.5 (DOUT); also elsewhere on the board
/LED_Controller6/GREEN: Q14.3 (C); also elsewhere on the board
/LED_Controller6/OUTB: R31.2, R33.1, U2.3 (OUTB)
/LED_Controller6/OUTG: R13.2, R15.1, U2.2 (OUTG)
/LED_Controller6/OUTR: R5.1, R12.2, U2.1 (OUTR)
/LED_Controller6/RED: Q2.3 (C); also elsewhere on the board
GND: C7.1, C8.1, C9.1, C10.1, U2.4 (GND), U3.4 (GND), U4.4 (GND), U5.4 (GND); also elsewhere on the board
unnamed: Q2.1 (B), Q7.3 (C), R5.2
unnamed: Q2.2 (E), Q7.1 (B), R14.2
unnamed: Q3.1 (B), Q8.3 (C), R6.2
unnamed: Q3.2 (E), Q8.1 (B), R24.2
unnamed: Q4.1 (B), Q9.3 (C), R7.2
unnamed: Q4.2 (E), Q9.1 (B), R34.2
unnamed: Q5.2 (E), Q10.1 (B), R44.2
unnamed: Q5.1 (B), Q10.3 (C), R8.2
unnamed: Q13.1 (B), Q14.2 (E), R16.2
unnamed: Q13.3 (C), Q14.1 (B), R15.2
unnamed: Q15.1 (B), Q16.2 (E), R19.2
unnamed: Q15.3 (C), Q16.1 (B), R18.2
unnamed: Q17.1 (B), Q18.2 (E), R23.2
unnamed: Q17.3 (C), Q18.1 (B), R21.2
unnamed: Q19.1 (B), Q20.2 (E), R27.2
unnamed: Q19.3 (C), Q20.1 (B), R26.2
unnamed: Q23.1 (B), Q24.2 (E), R35.2
unnamed: Q23.3 (C), Q24.1 (B), R33.2
unnamed: Q25.1 (B), Q26.2 (E), R38.2
unnamed: Q25.3 (C), Q26.1 (B), R37.2
unnamed: Q27.1 (B), Q28.2 (E), R41.2
unnamed: Q27.3 (C), Q28.1 (B), R40.2
unnamed: Q29.1 (B), Q30.2 (E), R46.2
unnamed: Q29.3 (C), Q30.1 (B), R45.2

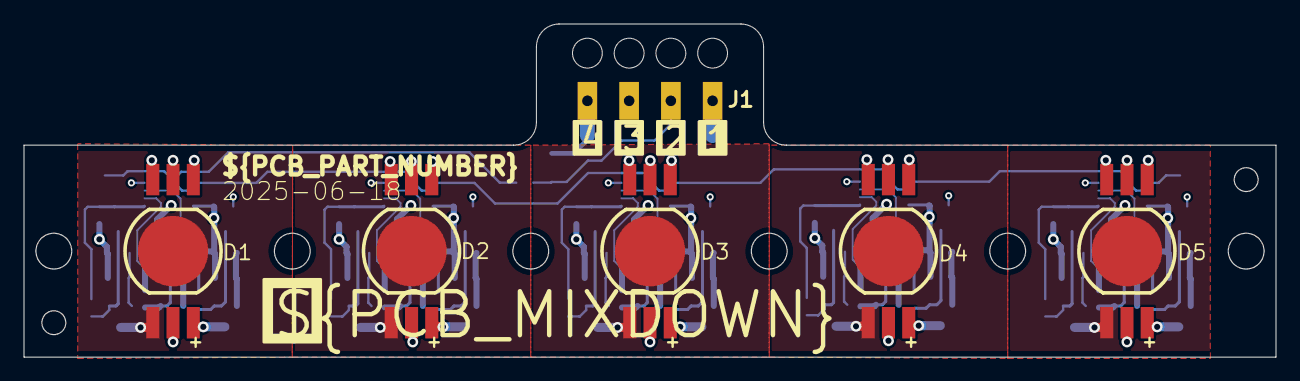
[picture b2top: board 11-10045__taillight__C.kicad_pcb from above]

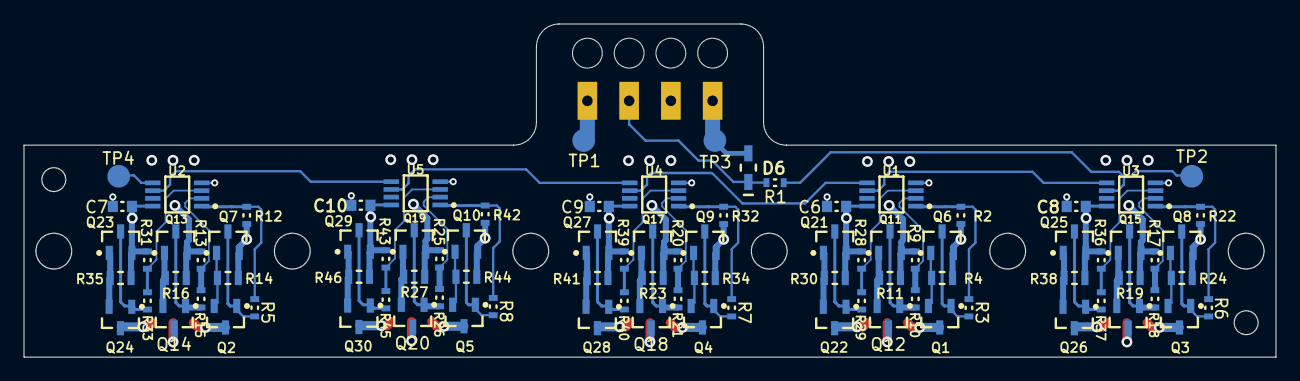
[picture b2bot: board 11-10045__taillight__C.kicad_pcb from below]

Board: 4 copper layers, 105.0 x 27.9 mm, 97 parts (91 on the bottom side), 69 nets.

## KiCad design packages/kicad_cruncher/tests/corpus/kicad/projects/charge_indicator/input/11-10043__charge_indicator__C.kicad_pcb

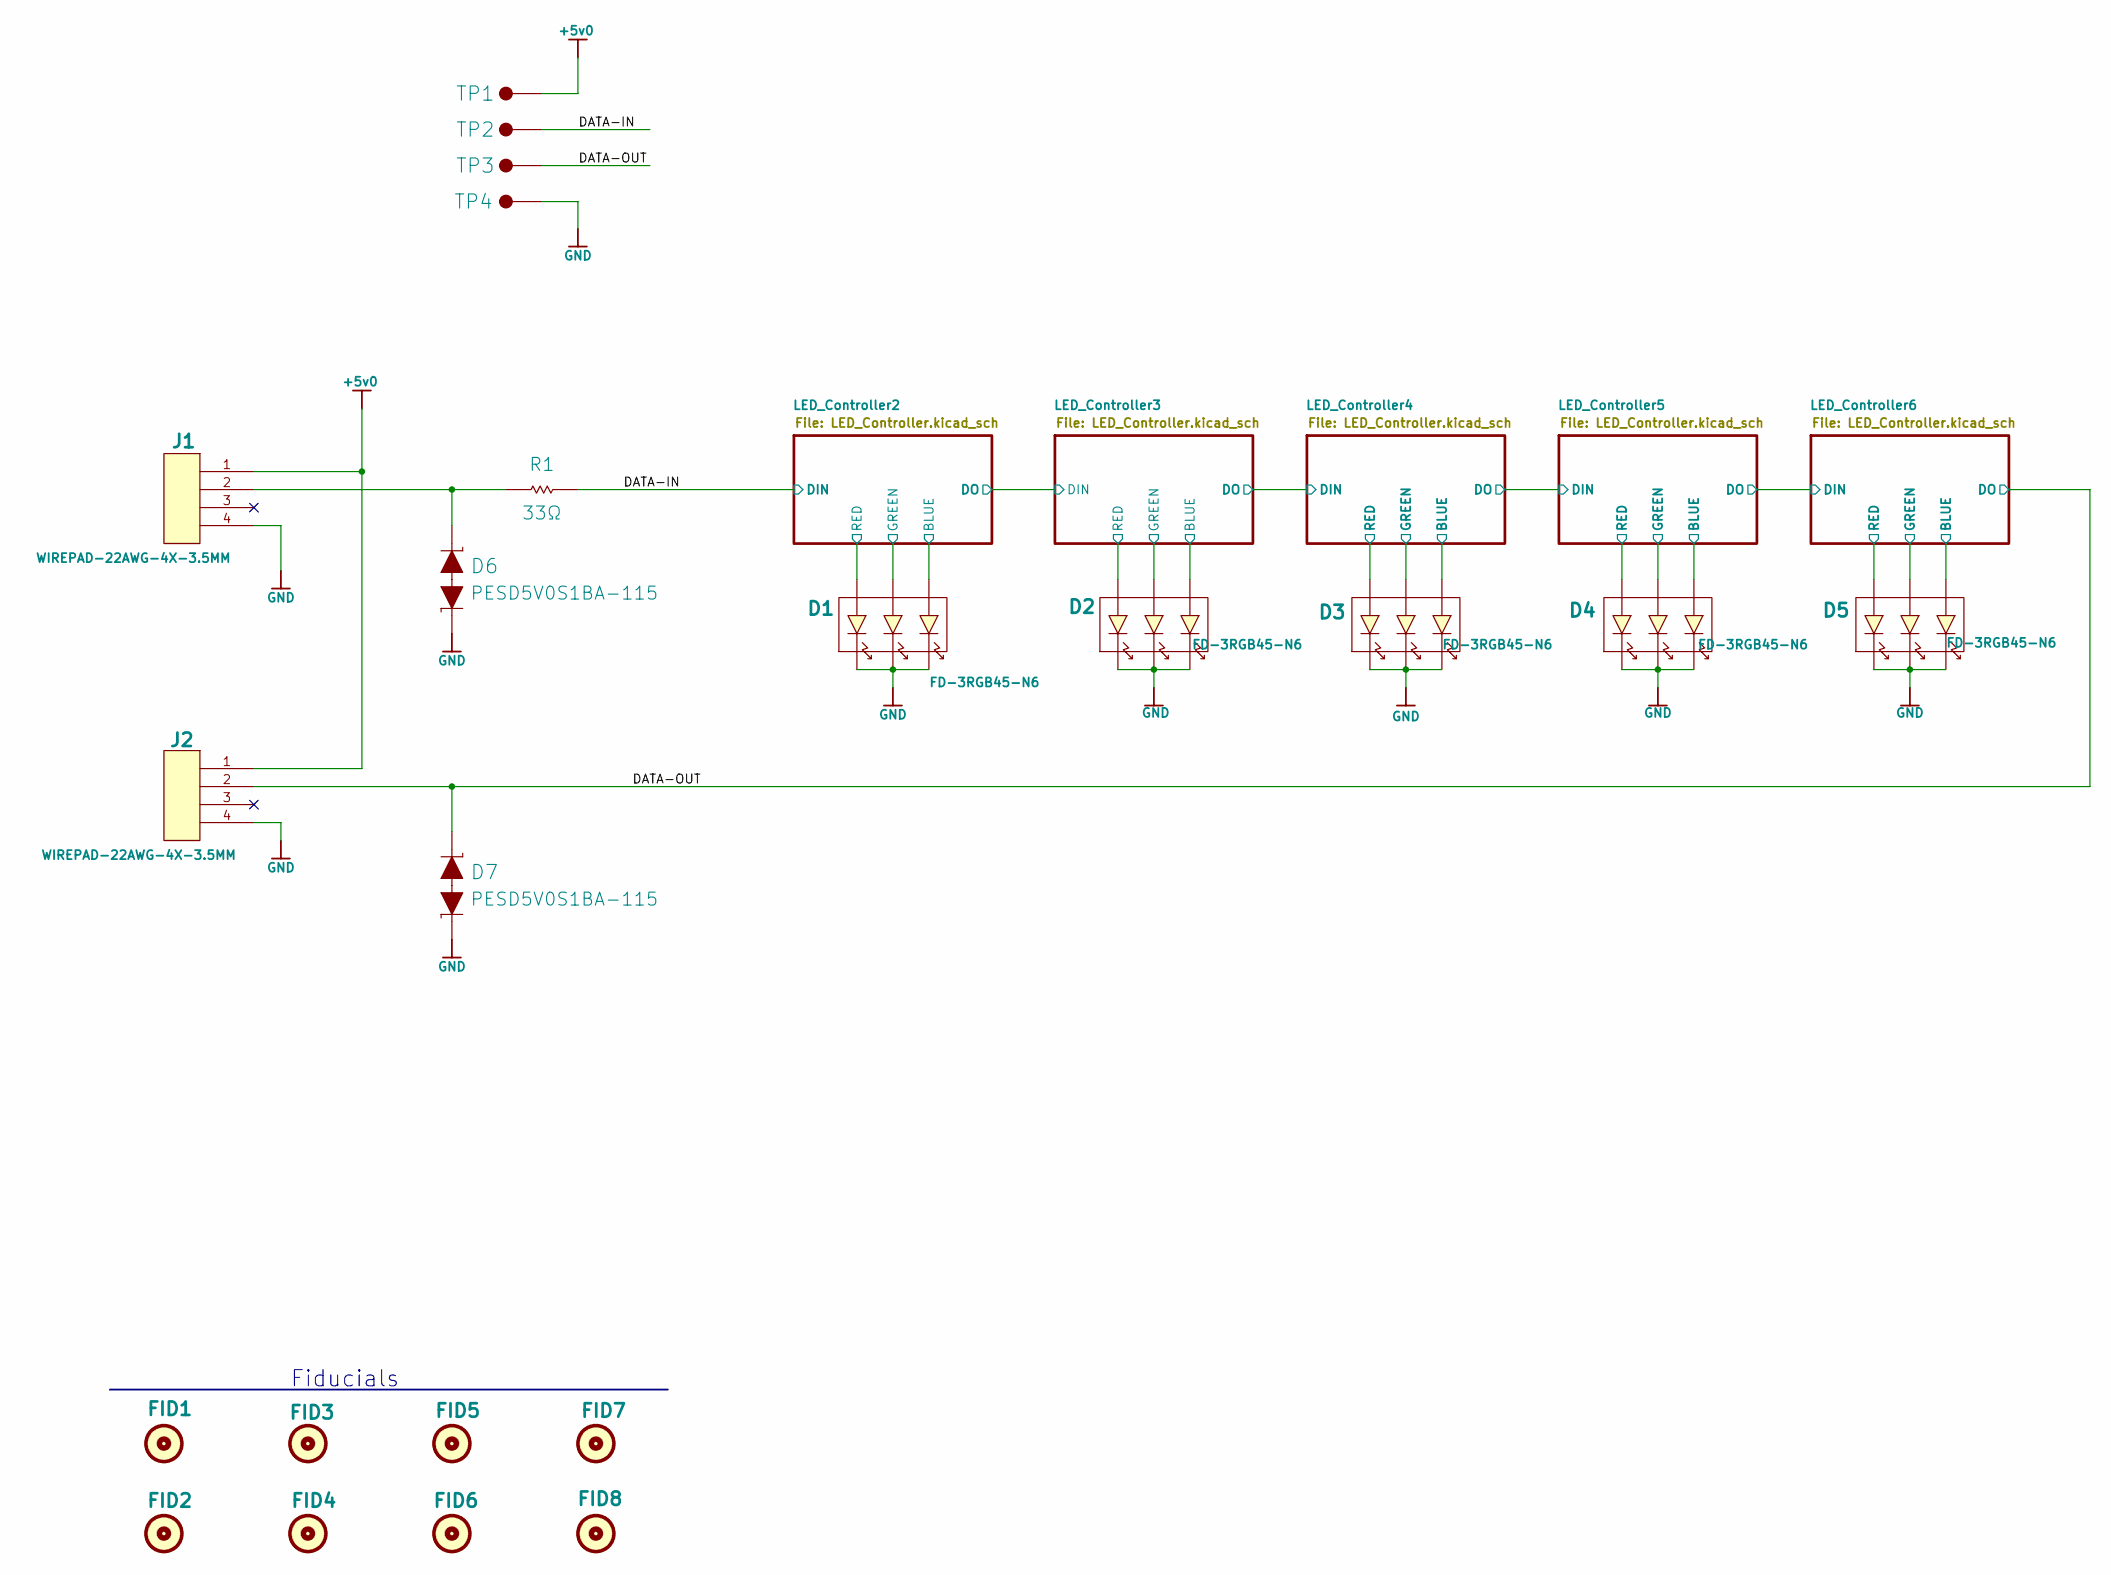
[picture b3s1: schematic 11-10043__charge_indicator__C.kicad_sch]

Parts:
D1, D2, D3, D4, D5: FD-3RGB45-N6; Manufacturer Part Number FD-3RGB45-N6
D6, D7: PESD5V0S1BA-115; D_SOD-323_P; Manufacturer Part Number PESD5V0S1BA-115
FID1, FID2, FID3, FID4, FID5, FID6, FID7, FID8: PCB Fiducial; fiducial-1mm-2mm; MANUFACTURER PART NUMBER fiducial-1mm-2mm
J1, J2: WIREPAD-22AWG-4X-3.5MM; Manufacturer Part Number WIREPAD-22AWG-4X-3.5MM
R1: 33Ω; R0603_0.55MM_MD; Manufacturer Part Number ERJ-3EKF33R0V
TP1, TP2, TP3, TP4: SMT Testpoint 1MM; SMT_TP-75; Manufacturer Part Number SMT_TP-75

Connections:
+5v0: J1.1, J2.1, TP1.1; also elsewhere on the board
/DATA-IN: R1.2, TP2.1; also elsewhere on the board
/DATA-OUT: D7.2 (C), J2.2, TP3.1; also elsewhere on the board
/LED_Controller2/BLUE: D1.B+; also elsewhere on the board
/LED_Controller2/GREEN: D1.G+; also elsewhere on the board
/LED_Controller2/RED: D1.R+; also elsewhere on the board
/LED_Controller3/BLUE: D2.B+; also elsewhere on the board
/LED_Controller3/GREEN: D2.G+; also elsewhere on the board
/LED_Controller3/RED: D2.R+; also elsewhere on the board
/LED_Controller4/BLUE: D3.B+; also elsewhere on the board
/LED_Controller4/GREEN: D3.G+; also elsewhere on the board
/LED_Controller4/RED: D3.R+; also elsewhere on the board
/LED_Controller5/BLUE: D4.B+; also elsewhere on the board
/LED_Controller5/GREEN: D4.G+; also elsewhere on the board
/LED_Controller5/RED: D4.R+; also elsewhere on the board
/LED_Controller6/BLUE: D5.B+; also elsewhere on the board
/LED_Controller6/GREEN: D5.G+; also elsewhere on the board
/LED_Controller6/RED: D5.R+; also elsewhere on the board
GND: D1.B-, D1.G-, D1.R-, D2.B-, D2.G-, D2.R-, D3.B-, D3.G-, D3.R-, D4.B-, D4.G-, D4.R-, D5.B-, D5.G-, D5.R-, D6.1 (C), D7.1 (C), J1.4, J2.4, TP4.1; also elsewhere on the board
unnamed: D6.2 (C), J1.2, R1.1

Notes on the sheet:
Fiducials
